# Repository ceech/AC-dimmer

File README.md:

# AC-dimmer

Additional description can be found here:https://www.ebay.com/itm/331824885028

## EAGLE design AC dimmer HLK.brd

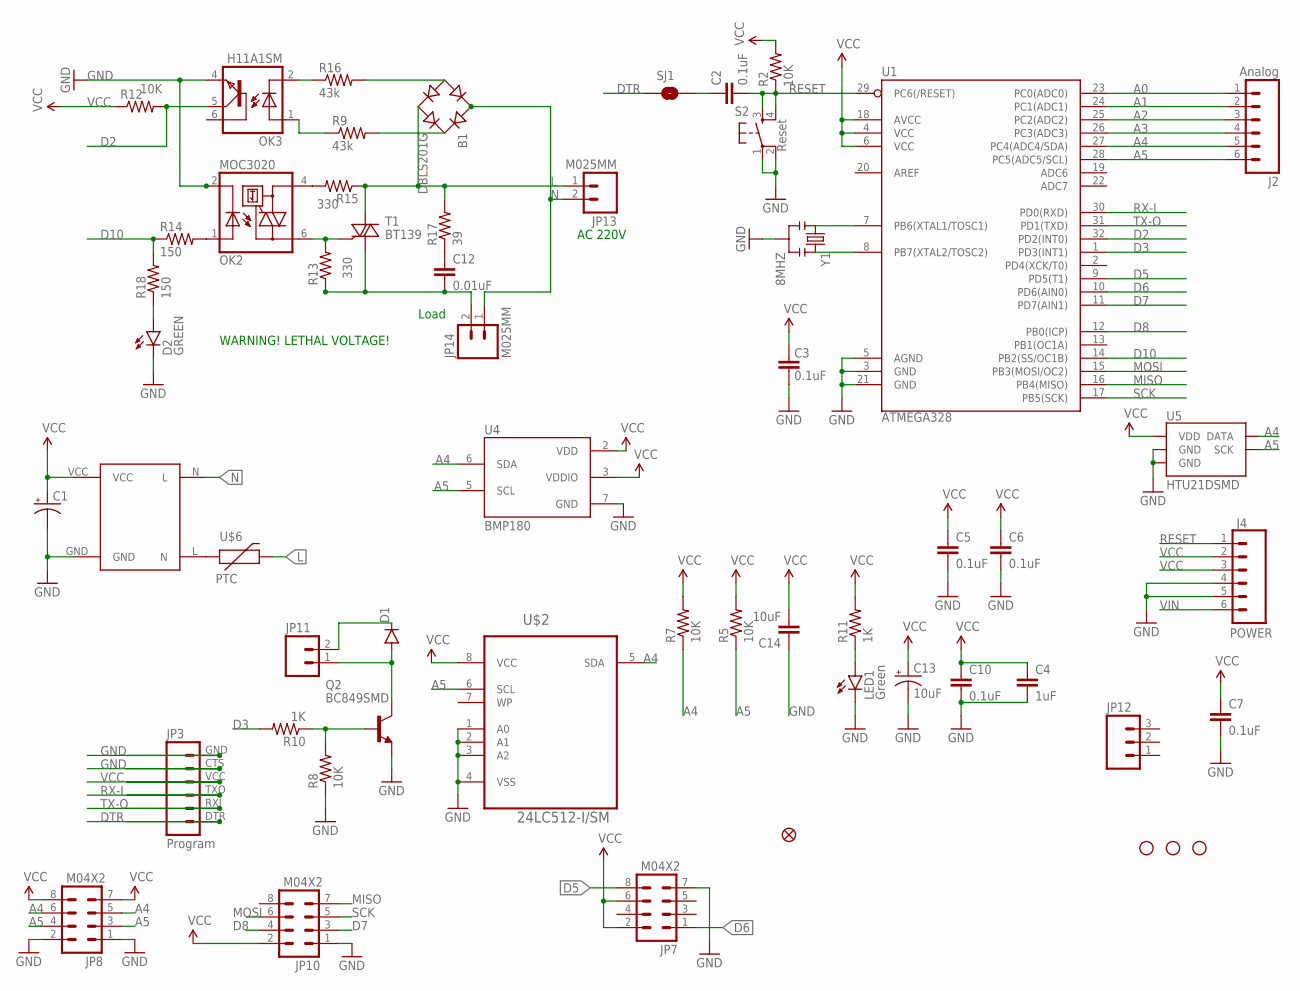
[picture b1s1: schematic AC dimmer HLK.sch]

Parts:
B1: DBLS201G; DBS
C1: CAP_POL3528-KIT; EIA3528-KIT
C2, C3, C5, C6, C7, C10: 0.1uF; 0805
C4: 1uF; 0805
C12: 0.01uF; C1206
C13: 10uF; EIA3216
C14: 10uF; 1206
D1: DIODESOD; SOD-323
D2: GREEN; LED-0603
J2: Analog; 1X06
J4: POWER; 1X06
JP2: FIDUCIAL1X2.5; FIDUCIAL-1X2.5
JP3: Program; 1X06
JP7, JP8, JP10: M04X2; 2X4
JP11: M02PTH; 1X02
JP12: M03PTH; 1X03
JP13, JP14: M025MM; SCREWTERMINAL-5MM-2
LED1: Green; LED-0603
OK2: MOC3020; DIL6-SMD
OK3: H11A1SM; DIL6-SMD
Q2: BC849SMD; SOT23-BEC
R2, R5, R7, R8: 10K; 0805
R9, R16: 43k; 1206
R10, R11: 1K; 0805
R12: RESISTOR0805-RES; 0805
R13, R15: RESISTOR1206; 1206
R14, R18: 150; 0805
R17: 39; 1206
S2: Reset; TACTILE_SWITCH_SMD
SJ1: SOLDERJUMPERNC2; SJ_2S-NOTRACE
T1: BT139; TO220AB
U1: ATMEGA328; TQFP32-08
U4: BMP180
U5: HTU21DSMD; HTU21D
U$2: 24LC512-I/SM; SOIC127P794X203-8N
U$3, U$9, U$10: STAND-OFFTIGHT; STAND-OFF-TIGHT
U$5: AC-DCHLK01; HLK-PM01
U$6: PTC; MC331XX
Y1: 8MHZ; RESONATOR-SMD

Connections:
A0: J2.1, U1.23 (PC0(ADC0))
A1: J2.2, U1.24 (PC1(ADC1))
A2: J2.3, U1.25 (PC2(ADC2))
A3: J2.4, U1.26 (PC3(ADC3))
A4: J2.5, JP8.5, JP8.6, R7.1, U1.27 (PC4(ADC4/SDA)), U4.6 (SDA), U5.DATA, U$2.5 (SDA)
A5: J2.6, JP8.3, JP8.4, R5.1, U1.28 (PC5(ADC5/SCL)), U4.5 (SCL), U5.SCK, U$2.6 (SCL)
D2: OK3.5 (COL), R12.2, U1.32 (PD2(INT0))
D3: R10.2, U1.1 (PD3(INT1))
D5: JP7.8, U1.9 (PD5(T1))
D6: JP7.1, U1.10 (PD6(AIN0))
D7: JP10.3, U1.11 (PD7(AIN1))
D8: JP10.4, U1.12 (PB0(ICP))
D10: R14.1, R18.2, U1.14 (PB2(SS/OC1B))
DTR: JP3.DTR (1), SJ1.1
GND: C1.C (-), C3.1, C4.2, C5.2, C6.2, C7.2, C10.2, C13.C (-), C14.1, D2.C, J4.4, J4.5, JP3.CTS (5), JP3.GND (6), JP7.7, JP8.1, JP8.2, JP10.1, LED1.C, OK2.2 (C), OK3.4 (EMI), Q2.E, R8.1, S2.1, S2.2, U1.3 (GND), U1.5 (AGND), U1.21 (GND), U4.7 (GND), U5.7 (GND), U5.GND, U$2.1 (A0), U$2.2 (A1), U$2.3 (A2), U$2.4 (VSS), U$5.GND, Y1.2
L: B1.AC2, JP13.1, R15.1, R17.2, T1.2 (A2), U$6.P$2 (2)
MISO: JP10.7, U1.16 (PB4(MISO))
MOSI: JP10.6, U1.15 (PB3(MOSI/OC2))
N: B1.AC1, JP13.2, JP14.1, U$5.N (L)
unnamed: C2.1, SJ1.2
unnamed: U1.7 (PB6(XTAL1/TOSC1)), Y1.1
unnamed: U1.8 (PB7(XTAL2/TOSC2)), Y1.3
unnamed: OK3.1 (A), R9.1
unnamed: U$5.L (N), U$6.P$1 (1)
unnamed: OK3.2 (C), R16.1
unnamed: LED1.A, R11.1
unnamed: B1.-, R16.2
unnamed: D1.A, JP11.1, Q2.C
unnamed: D1.C, JP11.2
unnamed: Q2.B, R8.2, R10.1
unnamed: B1.+, R9.2
unnamed: C12.2, JP14.2, R13.1, T1.1 (A1)
unnamed: OK2.6 (A2), R13.2, T1.3 (G)
unnamed: OK2.4 (A1), R15.2
unnamed: OK2.1 (A), R14.2
unnamed: C12.1, R17.1
unnamed: D2.A, R18.1
RESET: C2.2, J4.1, R2.1, S2.3, S2.4, U1.29 (PC6(/RESET))
RX-I: JP3.TXO (3), U1.30 (PD0(RXD))
SCK: JP10.5, U1.17 (PB5(SCK))
TX-O: JP3.RXI (2), U1.31 (PD1(TXD))
VCC: C1.A (+), C3.2, C4.1, C5.1, C6.1, C7.1, C10.1, C13.A (+), C14.2, J4.2, J4.3, JP3.VCC (4), JP7.2, JP7.6, JP8.7, JP8.8, JP10.2, R2.2, R5.2, R7.2, R11.2, R12.1, U1.4 (VCC), U1.6 (VCC), U1.18 (AVCC), U4.2 (VDD), U4.3 (VDDIO), U5.VDD, U$2.8 (VCC), U$5.VCC
VIN: J4.6

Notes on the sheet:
Load
AC 220V
WARNING! LETHAL VOLTAGE!

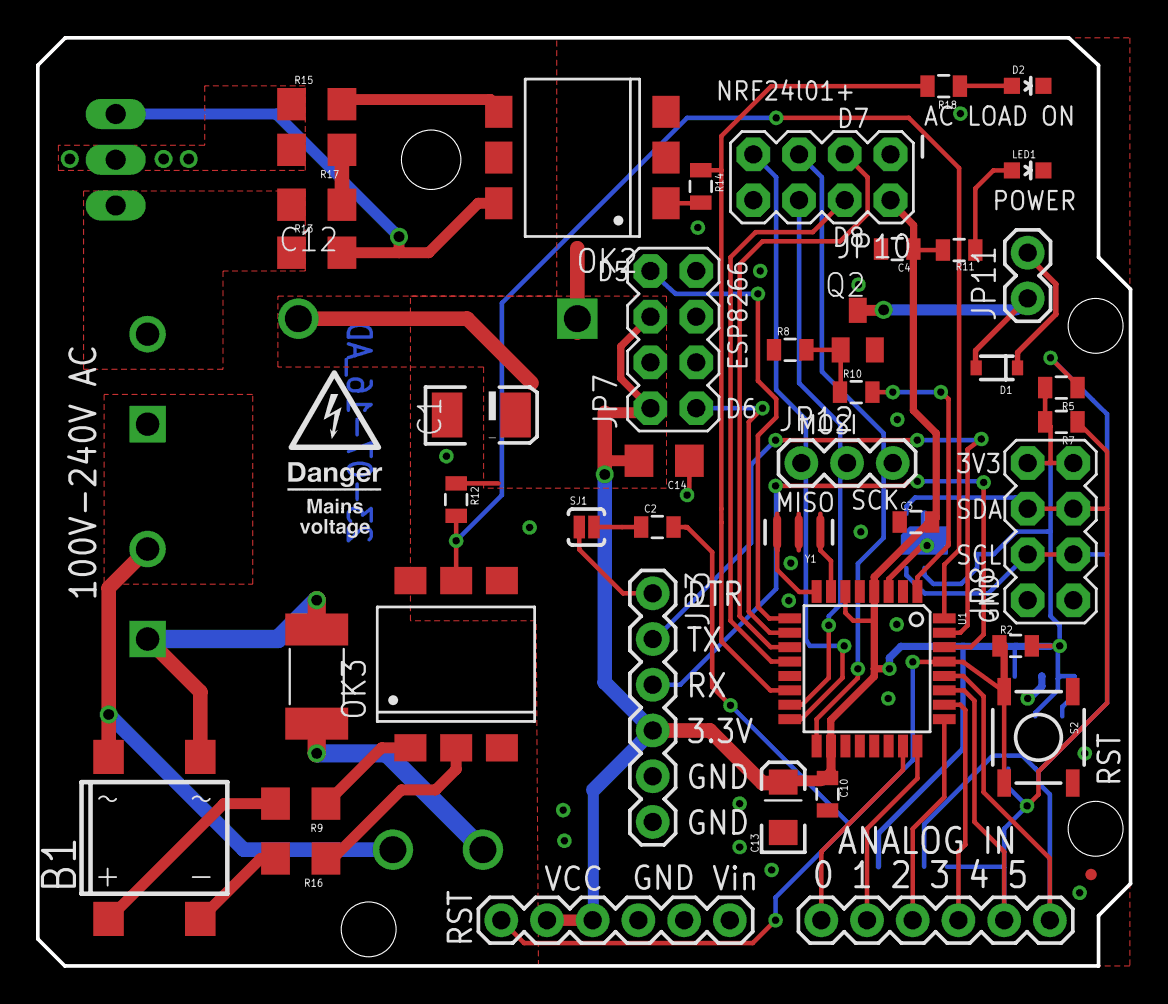
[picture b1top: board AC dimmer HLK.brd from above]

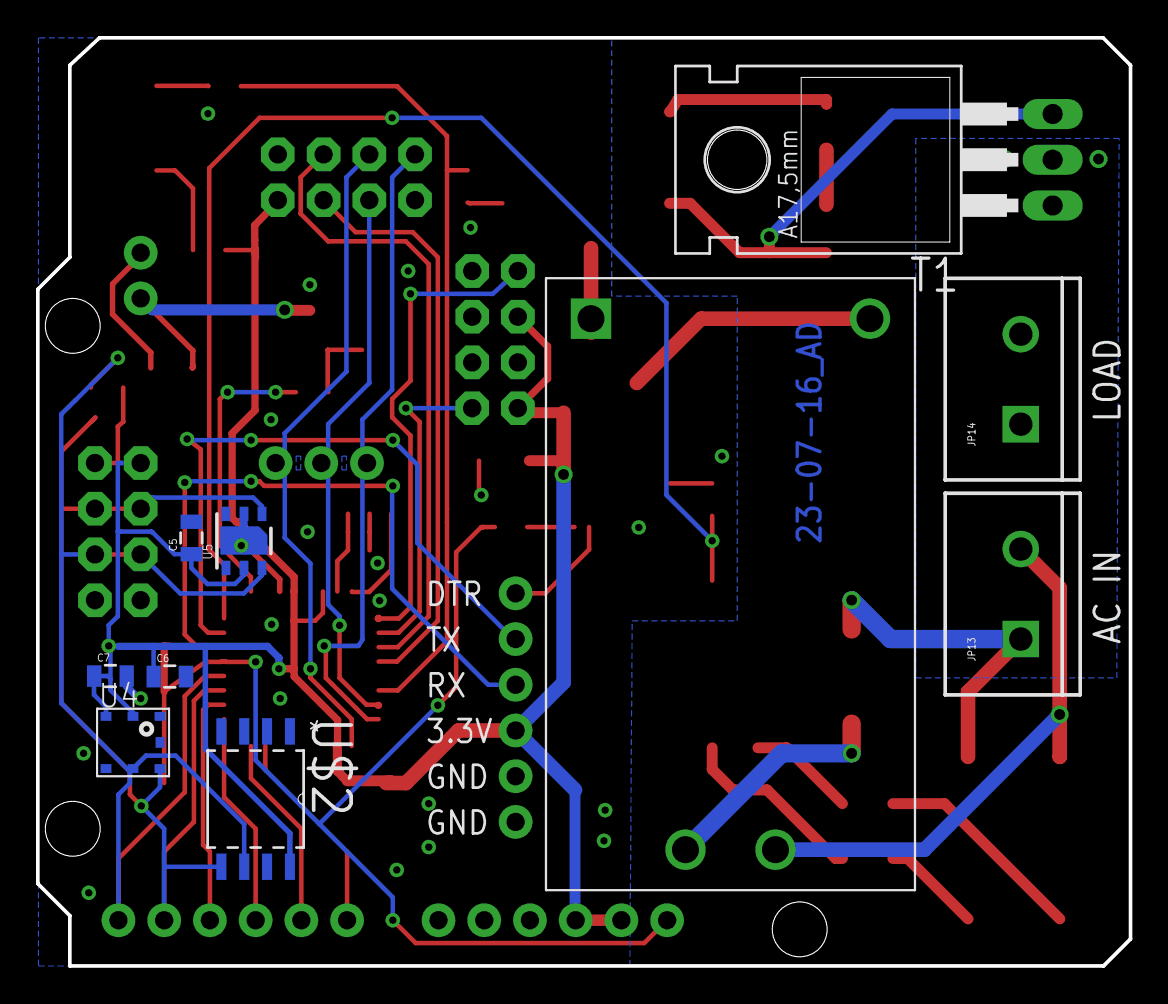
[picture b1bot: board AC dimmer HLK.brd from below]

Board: 2 copper layers, 60.7 x 51.6 mm, 57 parts (10 on the bottom side), 42 nets.

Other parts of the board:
U$4: WARNING_02

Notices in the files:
parts and their libraries:
SparkFun-Connectors: Licensing: Creative Commons ShareAlike 4.0 International - https://creativecommons.org/licenses/by-sa/4.0
